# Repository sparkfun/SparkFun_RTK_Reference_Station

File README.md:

SparkFun RTK Reference Station
========================================

<table class="table table-hover table-striped table-bordered">
  <tr align="center">
   <td></td>
  <tr align="center">
    <td><a href="https://www.sparkfun.com/products/22429">SparkFun RTK Reference Station (GPS-22429)</a></td>
  </tr>
</table>

The RTK Reference Station from SparkFun is our most capable GNSS receiver and logger to date. It's your one stop shop for high precision geolocation, surveying and time reference needs. For basic users, it is incredibly easy to get up and running; for advanced users, the Reference Station is a flexible and powerful tool. We took everything we learned while developing our other RTK products, refined it and the Reference Station is the end result.

Is this just a [RTK Facet](https://www.sparkfun.com/products/19984) in a metal box? Oh no! It is _so_ much more... Sure, it is based on the same ESP32-WROOM processor and u-blox ZED-F9P multi-band GNSS module as the Facet. And it runs the same core firmware as the rest of the RTK product family. But there the similarities end. The Reference Station has 10/100 Mbps Ethernet connectivity provided by a WIZnet W5500 and it can be powered by Power-over-Ethernet (PoE) too. With just a few minutes of setup and survey-in, your Reference Station can be serving RTCM correction data to an NTRIP caster of your choice, all via Ethernet!

Need an affordable Network Time Protocol time server for your Ethernet network? We've got you covered. The Reference Station can act as a NTP server. It supports DHCP by default, but you can give it a fixed IP address if you want to. DNS, gateway and subnet mask are all configurable too.

The Reference Station gets a big speed boost too. The microSD card socket is connected via full 4-bit SDIO instead of the usual SPI, providing an order or magnitude improvement in read and write speeds. Similarly, the u-blox ZED-F9P GNSS module is connected via SPI instead of the usual I2C, also providing an order of magnitude improvement in data transfer speeds. Need to log RAWX and SFRBX at 20Hz? You can with the Reference Station!

Repository Contents
-------------------

* [**/Reference_Station_Test_Sketches**](/Reference_Station_Test_Sketches/) - Stand-alone Arduino test sketches for the Reference Station
* [**/Hardware**](/Hardware/) - Eagle PCB files, schematic and dimensions
* [**/Enclosure**](/Enclosure/) - Mechanical drawings for the custom extruded aluminium case and machined panels
* [**/Front_Panel**](/Front_Panel/) - Eagle PCB files for the prototype (fit-check) front panel
* [**/Rear_Panel**](/Rear_Panel/) - Eagle PCB files for the prototype (fit-check) rear panel
* [**/Front_Panel_Sticker**](/Front_Panel_Sticker/) - Drawings and prototype (fit-check) files for the front sticker
* [**/Rear_Panel_Sticker**](/Rear_Panel_Sticker/) - Drawings and prototype (fit-check) files for the rear sticker
* [**/Sticker_Alignment_Jig__Panel**](/Sticker_Alignment_Jig__Panel/) - Eagle PCB files for the two-piece sticker alignment jig
* [**/Sticker_Alignment_Jig__Sticker**](/Sticker_Alignment_Jig__Sticker/) - Eagle PCB files for the two-piece sticker alignment jig

Documentation
--------------

* **[RTK Product Manual](https://docs.sparkfun.com/SparkFun_RTK_Firmware/)** - A detailed guide describing all the various software features of the RTK product line. Essentially it is a manual for the firmware used by the RTK Reference Station.
* **[RTK Reference Station Hookup Guide](https://learn.sparkfun.com/tutorials/sparkfun-rtk-reference-station-hookup-guide)** - Hookup guide for the SparkFun RTK Reference Station.

License Information
-------------------

This product is _**open source**_! 

Please review the LICENSE.md file for license information. 

If you have any questions or concerns on licensing, please contact technical support on our [SparkFun forums](https://forum.sparkfun.com/viewforum.php?f=152).

Distributed as-is; no warranty is given.

- Your friends at SparkFun.

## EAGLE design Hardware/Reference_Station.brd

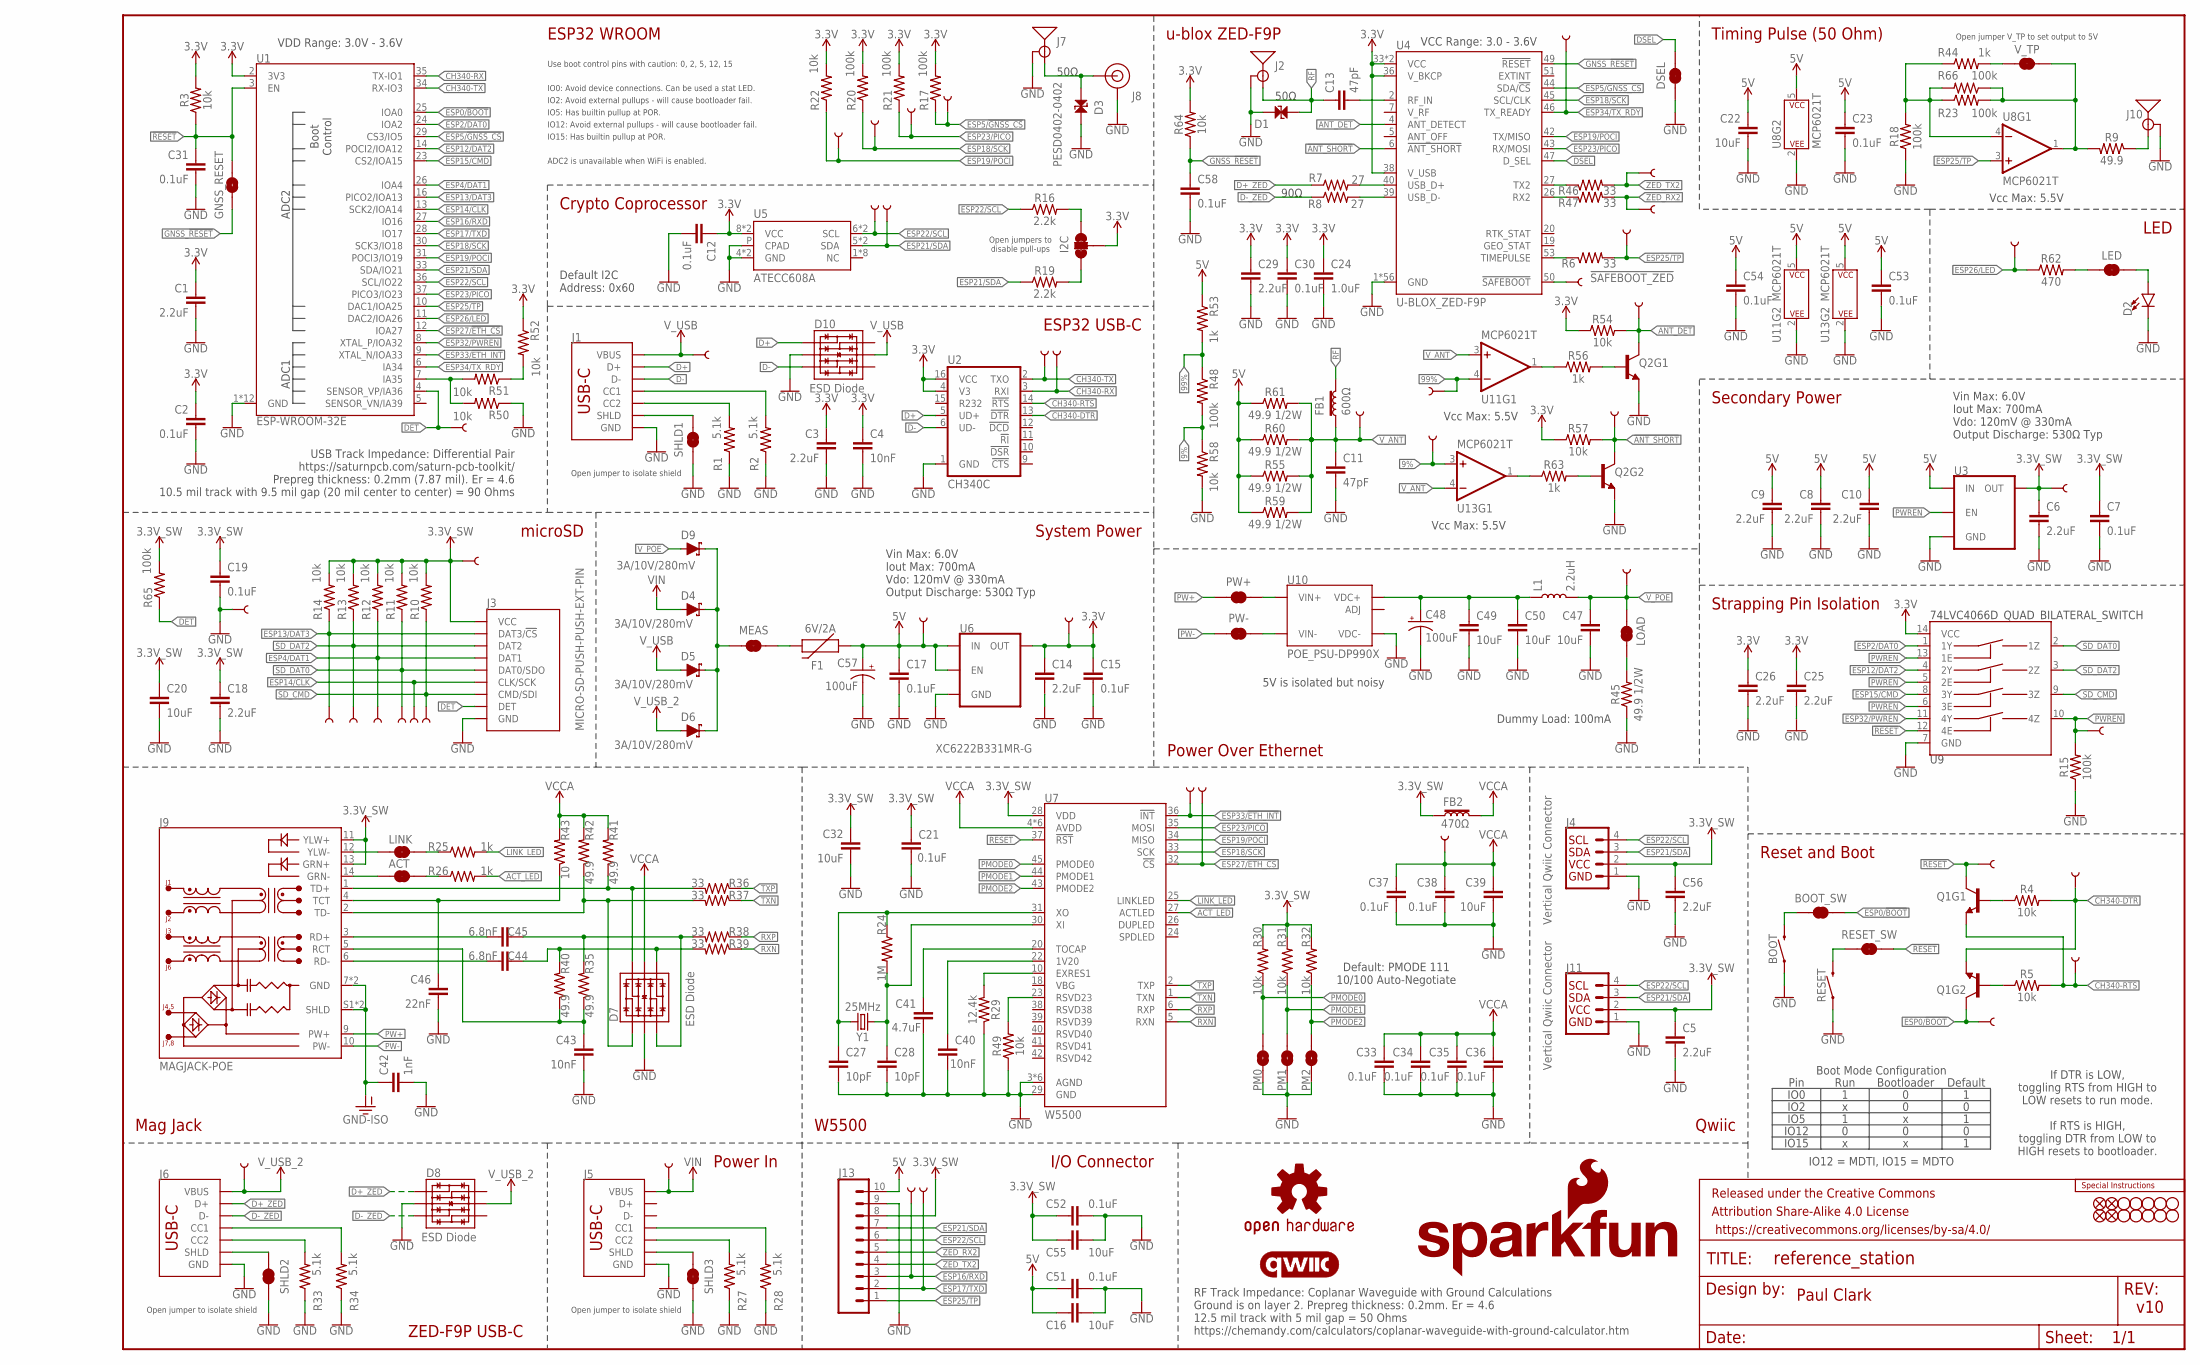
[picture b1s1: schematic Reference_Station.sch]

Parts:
3V3, 3V3_SW, 5V, 9%, 99%: TEST-POINTPOGO_PTH; 1X01_NO_SILK
!SAFEBOOT_ZED!: TEST-POINTPOGO_PTH; 1X01_NO_SILK
ACT: JUMPER-SMT_2_NC_TRACE_SILK; SMT-JUMPER_2_NC_TRACE_SILK
ANT_DET: TEST-POINTPOGO_PTH; 1X01_NO_SILK
ANT_SHT: TEST-POINTPOGO_PTH; 1X01_NO_SILK
BOOT: MOMENTARY-SWITCH-SPST-PTH-RIGHT-ANGLE-8-020; TACTILE_SWITCH_PTH_RA_8-020
BOOT_SW: JUMPER-SMT_2_NC_TRACE_SILK; SMT-JUMPER_2_NC_TRACE_SILK
C1, C3, C5, C6, C8, C9, C10, C14, C18, C25, C26, C29, C56: 2.2uF; 0603
C2, C7, C12, C15, C17, C19, C21, C23, C30, C31, C33, C34, C35, C36, C37, C38, C51, C52, C53, C54, C58: 0.1uF; 0603
C4, C40, C43: 10nF; 0603
C11, C13: 47pF; 0603
C16, C47, C49, C50: 10uF; 0805
C20, C22, C32, C39, C55: 10uF; 0603
C24: 1.0uF; 0603
C27, C28: 10pF; 0603
C41: 4.7uF; 0603
C42: 1nF; 1206
C44, C45: 6.8nF; 0603
C46: 22nF; 0603
C48, C57: 100uF; PANASONIC_D
CLK: TEST-POINTPOGO_PTH; 1X01_NO_SILK
CMD, CMD1: TEST-POINTPOGO_PTH; 1X01_NO_SILK
D1, D3: PESD0402-0402; 0402
D2: LED-RIGHT-ANGLE-PTH-GREEN; CBI-RIGHT-ANGLE-PTH
D4, D5, D6, D9: 3A/10V/280mV; SOD-323
D7, D8, D10: ESD Diode; SOT-23-6
DAT0, DAT1, DAT2, DAT3: TEST-POINTPOGO_PTH; 1X01_NO_SILK
DET: TEST-POINTPOGO_PTH; 1X01_NO_SILK
DSEL: JUMPER-SMT_2_NC_TRACE_SILK; SMT-JUMPER_2_NC_TRACE_SILK
DTR: TEST-POINTPOGO_PTH; 1X01_NO_SILK
ETH_CS: TEST-POINTPOGO_PTH; 1X01_NO_SILK
ETH_INT: TEST-POINTPOGO_PTH; 1X01_NO_SILK
F1: 6V/2A; 1210
FB1: 600Ω; 0805
FB2: 470Ω; 0603
FD1, FD2, FD3, FD4: FIDUCIAL1X2; FIDUCIAL-1X2
FRAME1: FRAME-LEDGER; CREATIVE_COMMONS
GND: TEST-POINTPOGO_PTH; 1X01_NO_SILK
GNSS_CS: TEST-POINTPOGO_PTH; 1X01_NO_SILK
GNSS_RESET: JUMPER-COMBO_2_NO; COMBO-JUMPER_2_NO
H1, H2, H3, H4, H5, H6, H7, H8, H9, H10: STAND-OFFTIGHT; STAND-OFF-TIGHT
I2C: JUMPER-SMT_3_2-NC_TRACE_SILK; SMT-JUMPER_3_2-NC_TRACE_SILK
J1, J5, J6: USB_C_4-LAYER_PADS; USB-C-16P_4LAYER-PADS
J2, J10: ANTENNA-SMA-GROUNDEDEDGE_SMA; SMA-EDGE
J3: MICRO-SD-PUSH-PUSH-EXT-PIN; MICROSD-EXTERNALPIN
J4, J11: Vertical Qwiic Connector; JST04_1MM_VERT
J7: ANTENNA-SMA-GROUNDEDEDGE_RPSMA; RP-SMA-EDGE
J8: U.FL2PIN-REDUCED-FOOTPRINT; U.FL_REDUCED_FOOTPRINT
J9: MAGJACK-POE; MAGJACK-SYM_LED
J13: CONN_10_3.5MM_RA_HEADER; 1X10_SCREW_TERMINAL_3.5MM
L1: 2.2uH; 0805-WIDE
LED: JUMPER-SMT_2_NC_TRACE_SILK; SMT-JUMPER_2_NC_TRACE_SILK
LINK: JUMPER-SMT_2_NC_TRACE_SILK; SMT-JUMPER_2_NC_TRACE_SILK
LOAD: JUMPER-SMT_2_NC_TRACE_SILK; SMT-JUMPER_2_NC_TRACE_SILK
LOGO1: SPECIAL_INSTRUCTIONS-ORDERING; ORDERING_INSTRUCTIONS
LOGO3: QWIIC_LOGO_6MM; QWIIC_6MM
LOGO4: OSHW-LOGOS; OSHW-LOGO-S
LOGO5: SFE_LOGO_NAME.2_INCH; SFE_LOGO_NAME_.2
LOGO6: SFE_LOGO_FLAME.2_INCH; SFE_LOGO_FLAME_.2
MEAS: JUMPER-COMBO_2_NC_TRACE; COMBO-JUMPER_2_NC_TRACE
PICO: TEST-POINTPOGO_PTH; 1X01_NO_SILK
PM0, PM1, PM2: JUMPER-SMT_2_NO_SILK; SMT-JUMPER_2_NO_SILK
POCI: TEST-POINTPOGO_PTH; 1X01_NO_SILK
PW+: JUMPER-COMBO_2_NC_TRACE; COMBO-JUMPER_2_NC_TRACE
PW-: JUMPER-COMBO_2_NC_TRACE; COMBO-JUMPER_2_NC_TRACE
PWREN: TEST-POINTPOGO_PTH; 1X01_NO_SILK
Q1, Q2: TRANS_NPN_DUAL-MBT3904DW1T1; SC70-6
R1, R2, R27, R28, R33, R34: 5.1k; 0603
R3, R4, R5, R10, R11, R12, R13, R14, R22, R30, R31, R32, R49, R50, R51, R52, R54, R57, R58, R64: 10k; 0603
R6, R36, R37, R38, R39, R46, R47: 33; 0603
R7, R8: 27; 0603
R9, R35, R40, R41, R42: 49.9; 0603
R15, R17, R18, R20, R21, R23, R48, R65, R66: 100k; 0603
R16, R19: 2.2k; 0603
R24: 1M; 0603
R25, R26, R44, R53, R56, R63: 1k; 0603
R29: 12.4k; 0603
R43: 10; 0603
R45, R55, R59, R60, R61: 49.9 1/2W; 1206
R62: 470; 0603
RESET: MOMENTARY-SWITCH-SPST-PTH-RIGHT-ANGLE-8-020; TACTILE_SWITCH_PTH_RA_8-020
RESET_SW: JUMPER-SMT_2_NC_TRACE_SILK; SMT-JUMPER_2_NC_TRACE_SILK
RTS: TEST-POINTPOGO_PTH; 1X01_NO_SILK
RX, RX2: TEST-POINTPOGO_PTH; 1X01_NO_SILK
RXD: TEST-POINTPOGO_PTH; 1X01_NO_SILK
SCK: TEST-POINTPOGO_PTH; 1X01_NO_SILK
SCL: TEST-POINTPOGO_PTH; 1X01_NO_SILK
SDA: TEST-POINTPOGO_PTH; 1X01_NO_SILK
SHLD1, SHLD2, SHLD3: JUMPER-SMT_2_NC_TRACE_SILK; SMT-JUMPER_2_NC_TRACE_SILK
TP: TEST-POINTPOGO_PTH; 1X01_NO_SILK
TP_BOOT: TEST-POINTPOGO_PTH; 1X01_NO_SILK
TP_LED: TEST-POINTPOGO_PTH; 1X01_NO_SILK
TP_RESET: TEST-POINTPOGO_PTH; 1X01_NO_SILK
TX, TX2: TEST-POINTPOGO_PTH; 1X01_NO_SILK
TXD: TEST-POINTPOGO_PTH; 1X01_NO_SILK
TX_RDY: TEST-POINTPOGO_PTH; 1X01_NO_SILK
U1: ESP-WROOM-32E; ESP-WROOM-32EU
U2: CH340C; SO016
U3, U6: XC6222B331MR-G; SOT23-5
U4: U-BLOX_ZED-F9P; ZED-F9P
U5: ATECC608A; DUAL_UDFN_2X3MM_SOIC-8
U7: W5500; LQFP-48
U8, U11, U13: MCP6021T; SOT23-5
U9: 74LVC4066D_QUAD_BILATERAL_SWITCH; SO14
U10: POE_PSU-DP990X; DP990X
VANT: TEST-POINTPOGO_PTH; 1X01_NO_SILK
VCCA: TEST-POINTPOGO_PTH; 1X01_NO_SILK
VIN: TEST-POINTPOGO_PTH; 1X01_NO_SILK
VPOE: TEST-POINTPOGO_PTH; 1X01_NO_SILK
VUSB, VUSB2: TEST-POINTPOGO_PTH; 1X01_NO_SILK
V_TP: JUMPER-SMT_2_NC_TRACE_SILK; SMT-JUMPER_2_NC_TRACE_SILK
Y1: 25MHz; CRYSTAL-SMD-2.0X1.6MM

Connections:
3.3V: 3V3.1, C1.1, C2.1, C3.1, C4.1, C12.1, C14.1, C15.1, C24.1, C25.1, C26.1, C29.1, C30.1, I2C.2, R3.2, R17.2, R20.2, R21.2, R22.2, R52.1, R54.1, R57.1, R64.2, U1.2 (3V3), U2.4 (V3), U2.16 (VCC), U4.33 (VCC), U4.34 (VCC), U4.36 (V_BKCP), U4.38 (V_USB), U5.8 (VCC), U5.8S (VCC), U6.5 (OUT), U9.14 (VCC)
3.3V_SW: 3V3_SW.1, C5.1, C6.1, C7.1, C18.1, C19.1, C20.1, C21.1, C32.1, C52.1, C55.1, C56.1, CMD1.1, FB2.1, J3.4 (VCC), J4.2, J9.11 (YLW+), J9.13 (GRN+), J11.2, J13.8, R10.2, R11.2, R12.2, R13.2, R14.2, R30.2, R31.2, R32.2, R65.2, U3.5 (OUT), U7.28 (VDD)
5V: 5V.1, C8.1, C9.1, C10.1, C16.1, C17.1, C22.1, C23.1, C51.1, C53.1, C54.1, C57.+, F1.1, J13.10, R53.1, R55.1, R59.1, R60.1, R61.1, U3.1 (IN), U6.1 (IN), U6.3 (EN), U8.5 (P$V+), U11.5 (P$V+), U13.5 (P$V+)
5V_RAW: C48.+, C49.1, C50.1, L1.1, U10.1 (VDC+), U10.2 (VDC+)
9%: 9%.1, R48.2, R58.1, U13.3 (+IN)
99%: 99%.1, R48.1, R53.2, U11.4 (-IN)
!ANT_SHORT!: ANT_SHT.1, Q2.6 (C), R57.2, U4.6 (!ANT_SHORT!)
!RESET!: C31.1, GNSS_RESET.2, GNSS_RESET.4 (2), Q1.3 (C), R3.1, RESET_SW.1, TP_RESET.1, U1.3 (EN), U7.37 (!RST!), U9.12 (4E)
!SAFEBOOT_ZED!: !SAFEBOOT_ZED!.1, U4.50 (!SAFEBOOT!)
ACT: ACT.1, J9.14 (GRN-)
ACT_LED: R26.2, U7.27 (ACTLED)
ANT_DET: ANT_DET.1, Q2.3 (C), R54.2, U4.4 (ANT_DETECT)
CH340-DTR: DTR.1, Q1.1 (E), R4.2, U2.13 (!DTR)
CH340-RTS: Q1.4 (E), R5.2, RTS.1, U2.14 (!RTS)
CH340-RX: TX.1, U1.35 (TX-IO1), U2.3 (RXI)
CH340-TX: RX.1, U1.34 (RX-IO3), U2.2 (TXO)
D+: D10.1 (IO1), J1.A6 (D+), J1.B6 (D+), U2.5 (UD+)
D+_ZED: D8.1 (IO1), J6.A6 (D+), J6.B6 (D+), R7.1
D-: D10.3 (IO2), J1.A7 (D-), J1.B7 (D-), U2.6 (UD-)
D-_ZED: D8.3 (IO2), J6.A7 (D-), J6.B7 (D-), R8.1
DET: DET.1, J3.9 (DET), R65.1, U1.4 (SENSOR_VP/IA36)
DSEL: DSEL.2, U4.47 (D_SEL)
ESP0/!BOOT!: BOOT_SW.1, Q1.6 (C), TP_BOOT.1, U1.25 (IOA0)
ESP2/DAT0: U1.24 (IOA2), U9.1 (1Y)
ESP4/DAT1: DAT1.1, J3.8 (DAT1), R12.1, U1.26 (IOA4)
ESP5/!GNSS_CS!: GNSS_CS.1, R17.1, U1.29 (CS3/IO5), U4.44 (SDA/!CS!)
ESP12/DAT2: U1.14 (POCI2/IOA12), U9.4 (2Y)
ESP13/DAT3: DAT3.1, J3.2 (DAT3/!CS!), R14.1, U1.16 (PICO2/IOA13)
ESP14/CLK: CLK.1, J3.5 (CLK/SCK), U1.13 (SCK2/IOA14)
ESP15/CMD: U1.23 (CS2/IOA15), U9.8 (3Y)
ESP16/RXD: J13.3, RXD.1, U1.27 (IO16)
ESP17/TXD: J13.2, TXD.1, U1.28 (IO17)
ESP18/SCK: R20.1, SCK.1, U1.30 (SCK3/IO18), U4.45 (SCL/CLK), U7.33 (SCK)
ESP19/POCI: POCI.1, R22.1, U1.31 (POCI3/IO19), U4.42 (TX/MISO), U7.34 (MISO)
ESP21/SDA: J4.3, J11.3, J13.7, R19.1, SDA.1, U1.33 (SDA/IO21), U5.5 (SDA), U5.5S (SDA)
ESP22/SCL: J4.4, J11.4, J13.6, R16.1, SCL.1, U1.36 (SCL/IO22), U5.6 (SCL), U5.6S (SCL)
ESP23/PICO: PICO.1, R21.1, U1.37 (PICO3/IO23), U4.43 (RX/MOSI), U7.35 (MOSI)
ESP25/TP: J13.1, R6.2, TP.1, U1.10 (DAC1/IOA25), U8.3 (+IN)
ESP26/LED: R62.1, TP_LED.1, U1.11 (DAC2/IOA26)
ESP27/!ETH_CS!: ETH_CS.1, U1.12 (IOA27), U7.32 (!CS!)
ESP32/PWREN: U1.8 (XTAL_P/IOA32), U9.11 (4Y)
ESP33/!ETH_INT!: ETH_INT.1, U1.9 (XTAL_N/IOA33), U7.36 (!INT!)
ESP34/TX_RDY: TX_RDY.1, U1.6 (IA34), U4.46 (TX_READY)
GND: BOOT.1, C1.2, C2.2, C3.2, C4.2, C5.2, C6.2, C7.2, C8.2, C9.2, C10.2, C11.2, C12.2, C14.2, C15.2, C16.2, C17.2, C18.2, C19.2, C20.2, C21.2, C22.2, C23.2, C24.2, C25.2, C26.2, C27.2, C28.2, C29.2, C30.2, C31.2, C32.2, C33.2, C34.2, C35.2, C36.2, C37.2, C38.2, C39.2, C40.2, C41.2, C42.2, C43.2, C46.2, C47.2, C48.-, C49.2, C50.2, C51.2, C52.2, C53.2, C54.2, C55.2, C56.2, C57.-, C58.2, D1.2, D2.C, D3.2, D7.2 (VSS), D8.2 (VSS), D10.2 (VSS), DSEL.1, GND.1, J1.GND, J1.GND2 (GND), J2.GND@0 (GND), J2.GND@1 (GND), J2.GND@2 (GND), J2.GND@3 (GND), J3.6 (GND), J3.10 (GND), J3.11 (GND), J3.12 (GND), J3.13 (GND), J4.1, J5.GND, J5.GND2 (GND), J6.GND, J6.GND2 (GND), J7.GND@0 (GND), J7.GND@1 (GND), J7.GND@2 (GND), J7.GND@3 (GND), J8.1 (GND), J8.2 (GND), J10.GND@0 (GND), J10.GND@1 (GND), J10.GND@2 (GND), J10.GND@3 (GND), J11.1, J13.9, PM0.1, PM1.1, PM2.1, Q2.1 (E), Q2.4 (E), R1.1, R2.1, R15.1, R18.1, R27.1, R28.1, R29.1, R33.1, R34.1, R45.1, R49.1, R50.1, R58.2, RESET.1, SHLD1.1, SHLD2.1, SHLD3.1, U1.1 (GND), U1.15 (GND), U1.38 (GND), U1.GND, U1.GNDT1 (GND), U1.GNDT2 (GND), U1.GNDT3 (GND), U1.GNDT4 (GND), U1.GNDT5 (GND), U1.GNDT6 (GND), U1.GNDT7 (GND), U1.GNDT8 (GND), U2.1 (GND), U3.2 (GND), U4.1 (GND), U4.3 (GND), U4.12 (GND), U4.14 (GND), U4.32 (GND), U4.37 (GND), U4.41 (GND), U4.48 (GND), U4.55 (GND), U4.56 (GND), U4.57 (GND), U4.58 (GND), U4.59 (GND), U4.60 (GND), U4.61 (GND), U4.62 (GND), U4.63 (GND), U4.64 (GND), U4.65 (GND), U4.66 (GND), U4.67 (GND), U4.68 (GND), U4.69 (GND), U4.70 (GND), U4.71 (GND), U4.72 (GND), U4.73 (GND), U4.74 (GND), U4.75 (GND), U4.76 (GND), U4.77 (GND), U4.78 (GND), U4.79 (GND), U4.80 (GND), U4.81 (GND), U4.82 (GND), U4.83 (GND), U4.84 (GND), U4.85 (GND), U4.86 (GND), U4.87 (GND), U4.88 (GND), U4.89 (GND), U4.90 (GND), U4.91 (GND), U4.92 (GND), U4.93 (GND), U4.94 (GND), U4.95 (GND), U4.96 (GND), U4.97 (GND), U4.98 (GND), U4.99 (GND), U4.100 (GND), U4.101 (GND), U4.102 (GND), U5.4 (GND), U5.4S (GND), U5.P (CPAD), U6.2 (GND), U7.3 (AGND), U7.9 (AGND), U7.14 (AGND), U7.16 (AGND), U7.19 (AGND), U7.29 (GND), U7.48 (AGND), U8.2 (P$V-), U9.7 (GND), U10.3 (VDC-), U11.2 (P$V-), U13.2 (P$V-)
GND-ISO: C42.1, J9.7 (GND), J9.8 (GND), J9.S1 (SHLD), J9.S2 (SHLD)
GNSS_!RESET!: C58.1, GNSS_RESET.1, GNSS_RESET.3 (1), R64.1, U4.49 (!RESET!)
LINK: J9.12 (YLW-), LINK.1
LINK_LED: R25.2, U7.25 (LINKLED)
MEAS: D4.C, D5.C, D6.C, D9.C, MEAS.2, MEAS.4 (2)
unnamed: J1.B5 (CC2), R1.2
unnamed: J1.A5 (CC1), R2.2
unnamed: R7.2, U4.40 (USB_D+)
unnamed: Q1.2 (B), R5.1
unnamed: Q1.5 (B), R4.1
unnamed: R8.2, U4.39 (USB_D-)
unnamed: LED.2, R62.2
unnamed: J6.SHLD1 (SHLD), J6.SHLD2 (SHLD), J6.SHLD3 (SHLD), J6.SHLD4 (SHLD), SHLD2.2
unnamed: J5.B5 (CC2), R27.2
unnamed: F1.2, MEAS.1, MEAS.3 (1)
unnamed: R46.1, U4.27 (TX2)
unnamed: ACT.2, R26.1
unnamed: D3.1, J7.SIG (SIGNAL), J8.FEED (SIGNAL)
unnamed: I2C.3, R16.2
unnamed: I2C.1, R19.2
unnamed: J10.SIG (SIGNAL), R9.1
unnamed: R18.2, R23.1, R44.1, R66.2, U8.4 (-IN)
unnamed: C27.1, R24.1, U7.31 (XO), Y1.1
unnamed: C28.1, R24.2, U7.30 (XI), Y1.3 (2)
unnamed: LINK.2, R25.1
unnamed: J5.A5 (CC1), R28.2
unnamed: R29.2, U7.10 (EXRES1)
unnamed: C40.1, U7.22 (1V20)
unnamed: C41.1, U7.20 (TOCAP)
unnamed: R9.2, R23.2, R66.1, U8.1 (OUT), V_TP.2
unnamed: LOAD.1, R45.2
unnamed: RESET.2, RESET_SW.2
unnamed: BOOT.2, BOOT_SW.2
unnamed: R49.2, U7.23 (RSVD23)
unnamed: R44.2, V_TP.1
unnamed: R47.1, U4.26 (RX2)
unnamed: J6.B5 (CC2), R33.2
unnamed: J6.A5 (CC1), R34.2
unnamed: R56.1, U11.1 (OUT)
unnamed: R6.1, U4.53 (TIMEPULSE)
unnamed: R50.2, R51.2, U1.7 (IA35)
unnamed: Q2.5 (B), R56.2
unnamed: R51.1, R52.2
unnamed: Q2.2 (B), R63.2
unnamed: R63.1, U13.1 (OUT)
unnamed: C13.2, U4.2 (RF_IN)
unnamed: J5.SHLD1 (SHLD), J5.SHLD2 (SHLD), J5.SHLD3 (SHLD), J5.SHLD4 (SHLD), SHLD3.2
unnamed: D2.A, LED.1
PMODE0: PM0.2, R30.1, U7.45 (PMODE0)
PMODE1: PM1.2, R31.1, U7.44 (PMODE1)
PMODE2: PM2.2, R32.1, U7.43 (PMODE2)
PW1+: PW+.1, PW+.3 (1), U10.5 (VIN+), U10.6 (VIN+)
PW1-: PW-.1, PW-.3 (1), U10.7 (VIN-), U10.8 (VIN-)
PW+: J9.9 (PW+), PW+.2, PW+.4 (2)
PW-: J9.10 (PW-), PW-.2, PW-.4 (2)
PWREN: PWREN.1, R15.2, U3.3 (EN), U9.5 (2E), U9.6 (3E), U9.10 (4Z), U9.13 (1E)
RCT: C43.1, J9.5 (RCT), R35.1, R40.1
RD+: C45.2, J9.3 (RD+)
RD-: C44.2, J9.6 (RD-)
RF: C13.1, D1.1, FB1.2, J2.SIG (SIGNAL)
RXN: R39.1, U7.5 (RXN)
RXN1: C44.1, D7.4 (IO3), R39.2, R40.2
RXP: R38.1, U7.6 (RXP)
RXP1: C45.1, D7.3 (IO2), R35.2, R38.2
SD_CMD: CMD.1, J3.3 (CMD/SDI), R10.1, U9.9 (3Z)
SD_DAT0: DAT0.1, J3.7 (DAT0/SDO), R11.1, U9.2 (1Z)
SD_DAT2: DAT2.1, J3.1 (DAT2), R13.1, U9.3 (2Z)
SHIELD: J1.SHLD1 (SHLD), J1.SHLD2 (SHLD), J1.SHLD3 (SHLD), J1.SHLD4 (SHLD), SHLD1.2
TCT: C46.1, J9.4 (TCT), R43.1
TD+: D7.6 (IO4), J9.1 (TD+), R36.2, R41.1
TD-: D7.1 (IO1), J9.2 (TD-), R37.2, R42.1
TXN: R37.1, U7.1 (TXN)
TXP: R36.1, U7.2 (TXP)
VCCA: C33.1, C34.1, C35.1, C36.1, C37.1, C38.1, C39.1, D7.5 (VCC), FB2.2, R41.2, R42.2, R43.2, U7.4 (AVDD), U7.8 (AVDD), U7.11 (AVDD), U7.15 (AVDD), U7.17 (AVDD), U7.21 (AVDD), VCCA.1
VIN: D4.A, J5.VBUS1 (VBUS), J5.VBUS2 (VBUS), VIN.1
V_ANT: C11.1, FB1.1, R55.2, R59.2, R60.2, R61.2, U11.3 (+IN), U13.4 (-IN), VANT.1
V_POE: C47.1, D9.A, L1.2, LOAD.2, VPOE.1
V_USB: D5.A, D10.5 (VCC), J1.VBUS1 (VBUS), J1.VBUS2 (VBUS), VUSB.1
V_USB_2: D6.A, D8.5 (VCC), J6.VBUS1 (VBUS), J6.VBUS2 (VBUS), VUSB2.1
ZED_RX2: J13.5, R47.2, RX2.1
ZED_TX2: J13.4, R46.2, TX2.1

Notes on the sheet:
ESP32 WROOM
ESP32 USB-C
Paul Clark
v10
Reset and Boot
LED
Secondary Power
System Power
microSD
Strapping Pin Isolation
W5500
Mag Jack
ZED-F9P USB-C
VDD Range: 3.0V - 3.6V
Vin Max: 6.0V Iout Max: 700mA Vdo: 120mV @ 330mA Output Discharge: 530Ω Typ
If DTR is LOW, toggling RTS from HIGH to LOW resets to run mode. If RTS is HIGH, toggling DTR from LOW to HIGH resets to bootloader.
Pin
IO0
IO2
IO12
IO15
IO5
Run
Bootloader
Default
IO12 = MDTI, IO15 = MDTO
Boot Mode Configuration
IO0: Avoid device connections. Can be used a stat LED.
ADC2 is unavailable when WiFi is enabled.
IO12: Avoid external pullups - will cause bootloader fail.
Use boot control pins with caution: 0, 2, 5, 12, 15
IO2: Avoid external pullups - will cause bootloader fail.
IO15: Has builtin pullup at POR.
IO5: Has builtin pullup at POR.
Open jumpers to disable pull-ups
Open jumper to isolate shield
50Ω
90Ω
u-blox ZED-F9P
VCC Range: 3.0 - 3.6V

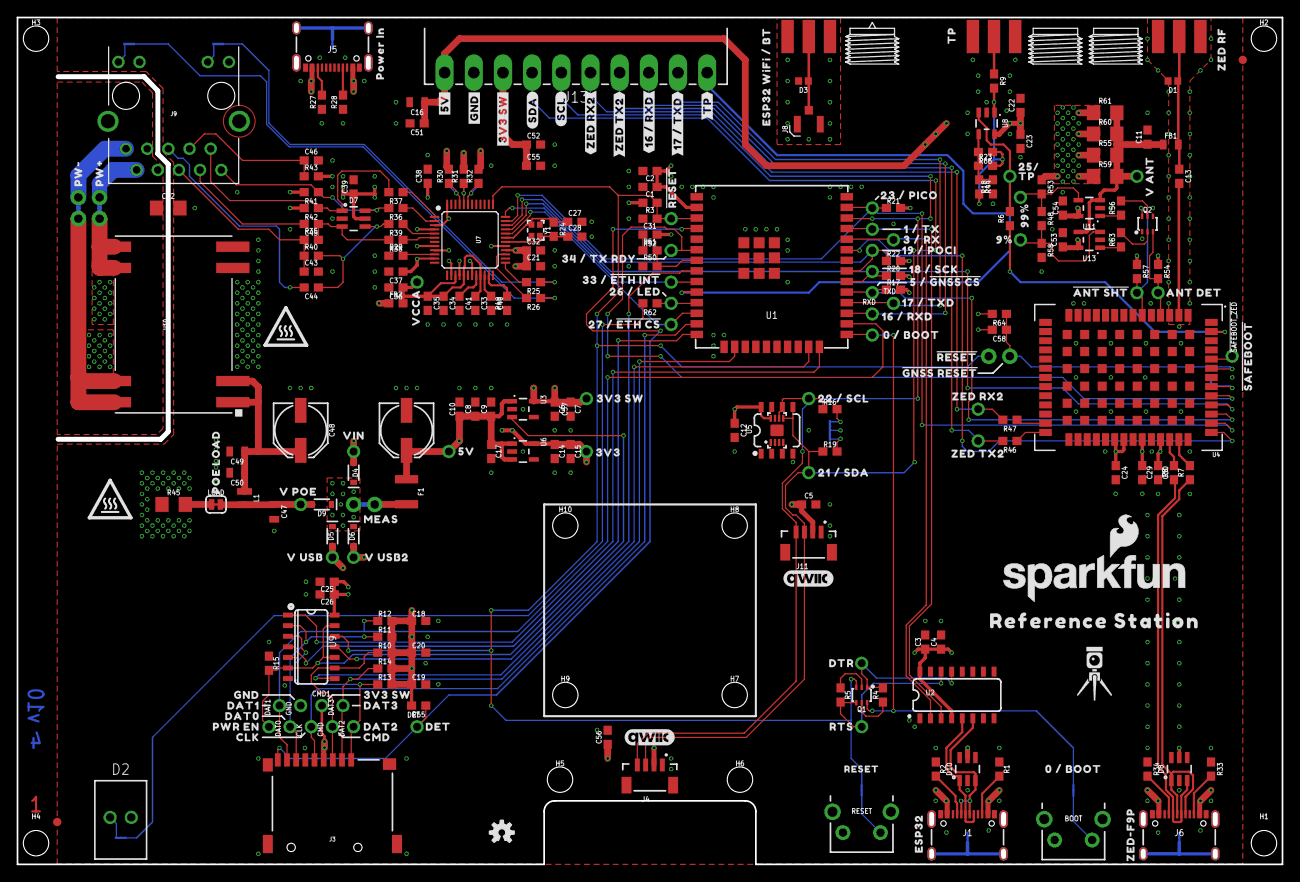
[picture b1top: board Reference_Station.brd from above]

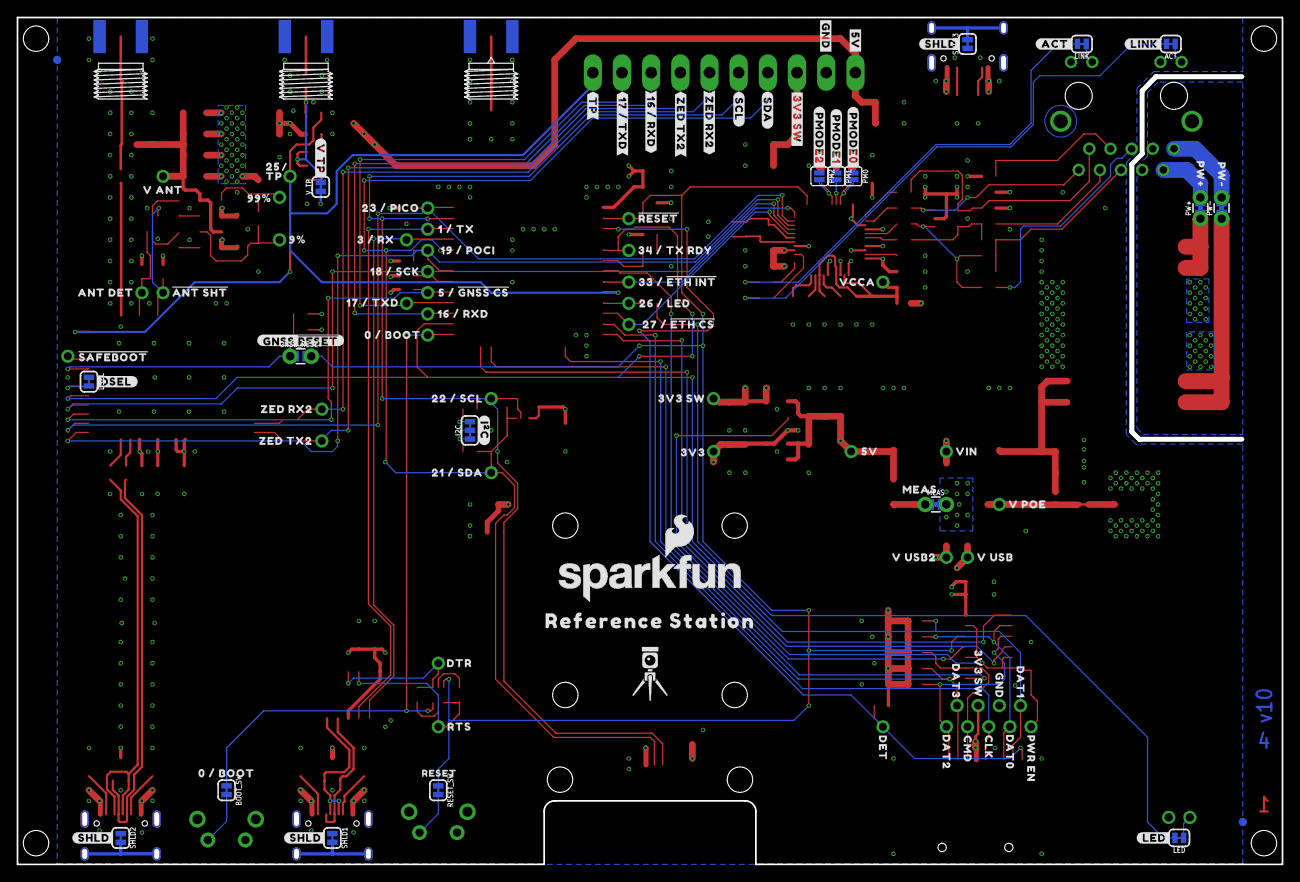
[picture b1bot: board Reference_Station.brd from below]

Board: 4 copper layers, 151.8 x 101.6 mm, 404 parts (98 on the bottom side), 125 nets.

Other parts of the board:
LOGO2: QWIIC_LOGO_6MM; QWIIC_6MM
LOGO7: SFE_LOGO_NAME.2_INCH; SFE_LOGO_NAME_.2
LOGO8: SFE_LOGO_FLAME.2_INCH; SFE_LOGO_FLAME_.2
U$2, U$148: RESET0
U$3, U$4, U$45: #SHLD#0
U$5, U$113: PW#0
U$6, U$114: PW#1
U$7, U$37, U$96, U$149: 0_#_BOOT0
U$8: POWER_IN0
U$9: #ACT#0
U$10: #LINK#1
U$11, U$115: #3V3_SW#0
U$12, U$124: #5V#0
U$13, U$123: #GND#6
U$14: #ZED_RX2#0
U$15, U$117: #SCL#8
U$16, U$116: #SDA#7
U$17: #ZED_RX2#3
U$18: #ZED_TX2#0
U$19: #ZED_TX2#3
U$20: #16_#_RXD#0
U$21: ESP32_WIFI_#_BT0
U$22: TP0
U$23: ZED_RF0
U$24, U$107: VCCA0
U$25, U$74, U$112: #RESET#0
U$26, U$108: 34_#_TX_RDY0
U$27, U$109: 33_#_#ETH_INT#0
U$28, U$110: 26_#_LED0
U$29, U$111: 27_#_#ETH_CS#0
U$30, U$98: 23_#_PICO23
U$31, U$89: 22_#_SCL20
U$32, U$102: 18_#_SCK6
U$33, U$101: 19_#_POCI19
U$34, U$99: 1_#_TX20
U$35, U$100: 3_#_RX20
U$36, U$97: 5_#_#GNSS_CS#1
U$38, U$90: 21_#_SDA24
U$39, U$91: ZED_RX224
U$40, U$92: ZED_TX2225
U$41, U$93: #SAFEBOOT#2226
U$42, U$94: ANT_DET2227
U$43, U$95: #ANT_SHT#2228
U$44, U$106: 9#2230
U$46: #I�C#0
U$47, U$104: 99#2230
U$48, U$103: TP2230
U$49, U$105: V_ANT2229
U$55, U$76: RTS2231
U$56, U$77: DTR2232
U$57, U$144: 3V3_SW15
U$58: #LED#2234
U$59, U$88: 3V3_SW25
U$60, U$87: 3V325
U$61, U$86: 5V25
U$62, U$84: MEAS2
U$63, U$85: VIN1
U$64, U$82: V_USB3
U$65, U$83: V_USB24
U$66, U$81: V_POE0
U$67: #PMODE0#0
U$68: #PMODE1#1
U$69: #PMODE2#2
U$70: #GNSS_#RESET##0
U$71: #V_TP#3
U$72: #DSEL#0
U$73, U$75: REFERENCE_STATION1
U$78: ESP320
U$79: ZED#F9P321
U$80, U$141: PWR_EN2233
U$118: #16_#_RXD#17
U$119: #17_#_TXD#0
U$120: #17_#_TXD#18
U$121: #TP#0
U$122: #TP#1
U$125, U$126: 16_#_RXD18
U$127, U$128: 17_#_TXD0
U$129, U$139: CLK13
U$130, U$138: CMD14
U$131, U$142: DAT10
U$132, U$140: DAT011
U$133, U$145: DAT315
U$134, U$137: DAT2316
U$135, U$143: GND12
U$136: POE_LOAD0
U$146, U$147: HIGH_TEMP_WARNING
U$150, U$151: 250
U$152, U$153: RTK5#SVG0
U$154: #GNSS_RESET#0
U$155, U$156: DET0

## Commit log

2022-11-29 Initial commit for proto review
2022-12-02 v01 after proto review
2022-12-02 Update schematic
2022-12-02 Add front and rear panel v2
2022-12-05 Add SMA Jig
2022-12-08 Add CONN-17279
2022-12-28 Add front panel PCB
2022-12-29 Add rear panel and gerbers
2022-12-29 Add panel png's and dxf's
2022-12-29 Add panel sticker files
2022-12-30 Update OLED and Ethernet
2022-12-30 Add SMA alignment jig
2022-12-30 Add sticker alignment jig
2023-01-11 Change ESP32 SMA to RP
2023-01-21 Add test sketches
2023-01-24 Add Ethernet example
2023-01-24 Add NTP_Server example
2023-01-26 Update NTP_Server example
2023-02-01 Update NTP_Server example - add Assist Now
2023-02-02 Split into multiple .ino's. Use multiple Assist Now GETs
2023-02-06 NTP Server: Assist Now improvements
2023-02-09 Shrink OLED cut-out by 0.3mm
2023-02-09 Reduce USB clearance to +/- 0.25mm (was +/- 0.5mm)
2023-02-09 Reduce button hole size
2023-02-09 Reduce LED hole size
2023-02-09 Reduce SMA hole diameter
2023-02-09 Reduce Ethernet clearance
2023-02-09 Reduce panel hole spacing by 0.3mm to match as-manufactured hole positions
2023-02-10 Update sticker alignment jig
2023-02-10 Update panels
2023-02-10 Update stickers
2023-02-10 v10 Hardware
2023-02-13 Improve TP output at 5V
2023-03-21 Move BOOT / MODE button further out. Update panels and stickers
2023-03-22 NTP_Server updates for ESP32 v2.0.2
2023-03-24 NTP Server - add TIM TP
2023-04-24 Replace OPA344 with MCP6021T-E/OT
2023-05-17 Change LED to GREEN
2023-06-22 Add README

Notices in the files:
parts and their libraries:
SparkFun-Capacitors: Licensing: Creative Commons ShareAlike 4.0 International - https://creativecommons.org/licenses/by-sa/4.0
SparkFun-Aesthetics: Released under the Creative Commons Attribution Share-Alike 4.0 License
SparkFun-Aesthetics: https://creativecommons.org/licenses/by-sa/4.0
